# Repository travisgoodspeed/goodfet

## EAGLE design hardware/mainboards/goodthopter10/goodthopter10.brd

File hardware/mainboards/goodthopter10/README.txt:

DIRECTORY STRUCTURE:
/bom - Contains Bill of Materials, Including DigiKey Part numbers
/grb - Gerber Files, Zipped and Packaged Ready-to-be-Sent to PCB Manufacturer
/lbr - Library files created for this project

--

If you like this project, the following will humbly accept beer donations:

Project Lead:
 Andrew Righter

Design and Schematic:
 Andrew Righter
 Travis Goodspeed

Board and Routing:
 Ryan Barnes

CAN Hacking Inspired By:
-Late night drinking in the Midwest with atlas and cutaway

This is the sexy GoodFET CAN Adapter, its purpose is to build an adapter that can handle CAN 
connection from an automobile or ECU into a laptop leveraging the maturing GoodFET firmware and project. 

Future releases may include radio (RF) hardware appliable to vehicle applications and other fun things, 
if you have any questions/comments:

andrew@215LAB.com

bugs/development:
goodfet-devel@lists.sourceforge.net

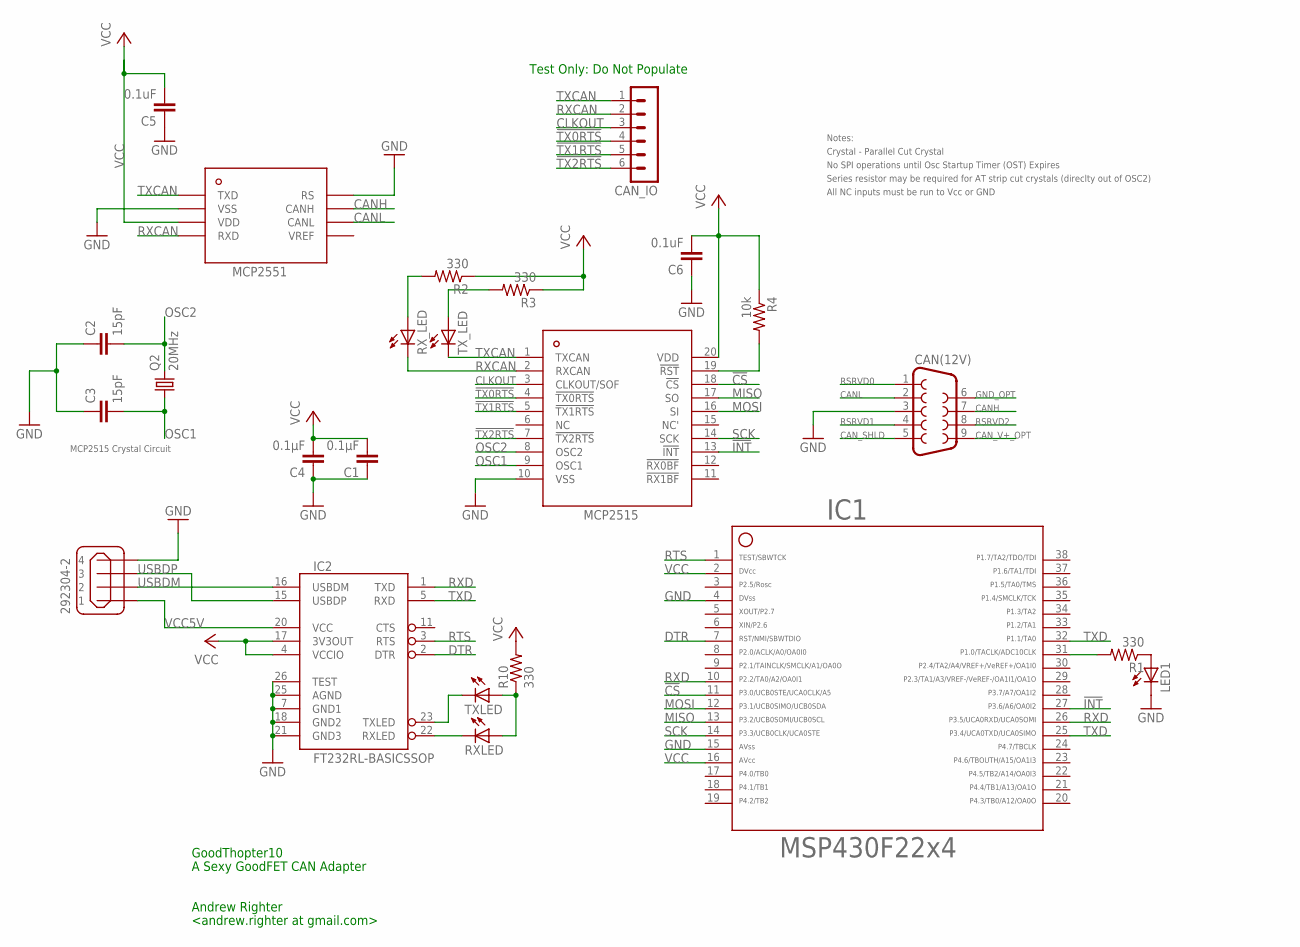
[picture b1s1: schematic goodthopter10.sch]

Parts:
292304-2: MINI-USB_4P-292304-2; 85-32004-10X
C1, C4: 0.1µF; C0603
C2, C3: 15pF; C0603
C5, C6: 0.1uF; C0603
CAN(12V): DB9MALE; DB9_MALE
CAN_IO: MA06-1
IC1: F22X4---DA38; DA38
IC2: FT232RL-BASICSSOP; SSOP28DB
LED1: LEDCHIP-LED0603; CHIP-LED0603
Q2: 20MHz; HC49UP
R1, R2, R3, R10: 330; R0603
R4: 10k; R0603
RXLED: LEDCHIP-LED0603; CHIP-LED0603
RX_LED: LEDCHIP-LED0603; CHIP-LED0603
TXLED: LEDCHIP-LED0603; CHIP-LED0603
TX_LED: LEDCHIP-LED0603; CHIP-LED0603
U$1: MCP2515; TSSOP20
U$2: MCP2551; SOIC-8

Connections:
!CS: IC1.11, U$1.18 (!CS)
!INT: IC1.27, U$1.13 (!INT)
!TX0RTS: CAN_IO.4, U$1.4 (!TX0RTS)
!TX1RTS: CAN_IO.5, U$1.5 (!TX1RTS)
!TX2RTS: CAN_IO.6, U$1.7 (!TX2RTS)
CANH: CAN(12V).7, U$2.CANH
CANL: CAN(12V).2, U$2.CANL
CAN_SHLD: CAN(12V).5
CAN_V+_OPT: CAN(12V).9
CLKOUT: CAN_IO.3, U$1.3 (CLKOUT/SOF)
DTR: IC1.7, IC2.2 (DTR)
GND: 292304-2.4, C1.1, C2.1, C3.1, C4.1, C5.1, C6.1, CAN(12V).3, IC1.4, IC1.15, IC2.7 (GND1), IC2.18 (GND2), IC2.21 (GND3), IC2.25 (AGND), IC2.26 (TEST), LED1.C, U$1.10 (VSS), U$2.RS, U$2.VSS
GND_OPT: CAN(12V).6
MISO: IC1.13, U$1.17 (SO)
MOSI: IC1.12, U$1.16 (SI)
unnamed: R2.2, RX_LED.A
unnamed: R3.2, TX_LED.A
unnamed: R4.2, U$1.19 (!RST)
unnamed: IC2.22 (RXLED), RXLED.C
unnamed: IC2.23 (TXLED), TXLED.C
unnamed: R10.1, RXLED.A, TXLED.A
unnamed: IC1.31, R1.2
unnamed: LED1.A, R1.1
OSC1: C3.2, Q2.1, U$1.9 (OSC1)
OSC2: C2.2, Q2.2, U$1.8 (OSC2)
RSRVD0: CAN(12V).1
RSRVD1: CAN(12V).4
RSRVD2: CAN(12V).8
RTS: IC1.1, IC2.3 (RTS)
RXCAN: CAN_IO.2, RX_LED.C, U$1.2 (RXCAN), U$2.RXD
RXD: IC1.10, IC1.26, IC2.1 (TXD)
SCK: IC1.14, U$1.14 (SCK)
TXCAN: CAN_IO.1, TX_LED.C, U$1.1 (TXCAN), U$2.TXD
TXD: IC1.25, IC1.32, IC2.5 (RXD)
USBDM: 292304-2.2, IC2.16 (USBDM)
USBDP: 292304-2.3, IC2.15 (USBDP)
VCC: C1.2, C4.2, C5.2, C6.2, IC1.2, IC1.16, IC2.4 (VCCIO), IC2.17 (3V3OUT), R2.1, R3.1, R4.1, R10.2, U$1.20 (VDD), U$2.VDD
VCC5V: 292304-2.1, IC2.20 (VCC)

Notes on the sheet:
GoodThopter10
A Sexy GoodFET CAN Adapter
Andrew Righter
<andrew.righter at gmail.com>
Crystal - Parallel Cut Crystal
Notes:
No SPI operations until Osc Startup Timer (OST) Expires
Series resistor may be required for AT strip cut crystals (direclty out of OSC2)
MCP2515 Crystal Circuit
292304-2
All NC inputs must be run to Vcc or GND
Test Only: Do Not Populate

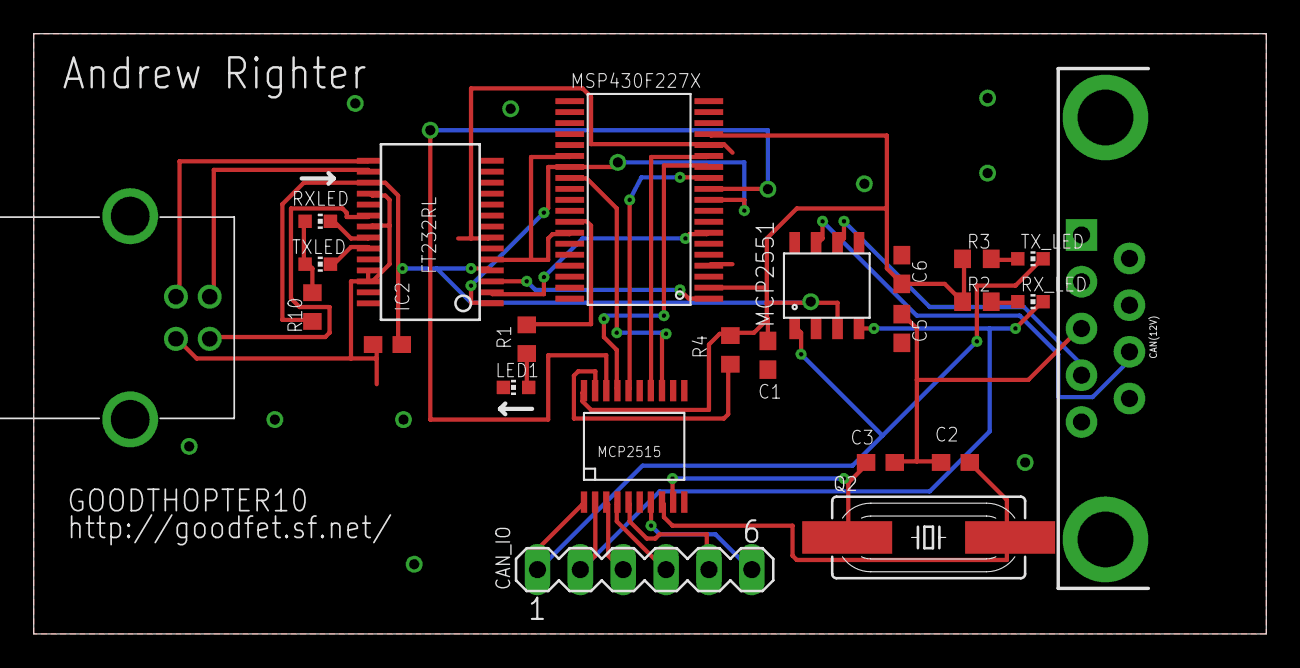
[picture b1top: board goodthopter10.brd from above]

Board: 2 copper layers, 73.0 x 35.6 mm, 24 parts (0 on the bottom side), 32 nets.

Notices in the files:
parts and their libraries:
SparkFun-Connectors: Licensing: CC v3.0 Share-Alike You are welcome to use this library for commercial purposes.
